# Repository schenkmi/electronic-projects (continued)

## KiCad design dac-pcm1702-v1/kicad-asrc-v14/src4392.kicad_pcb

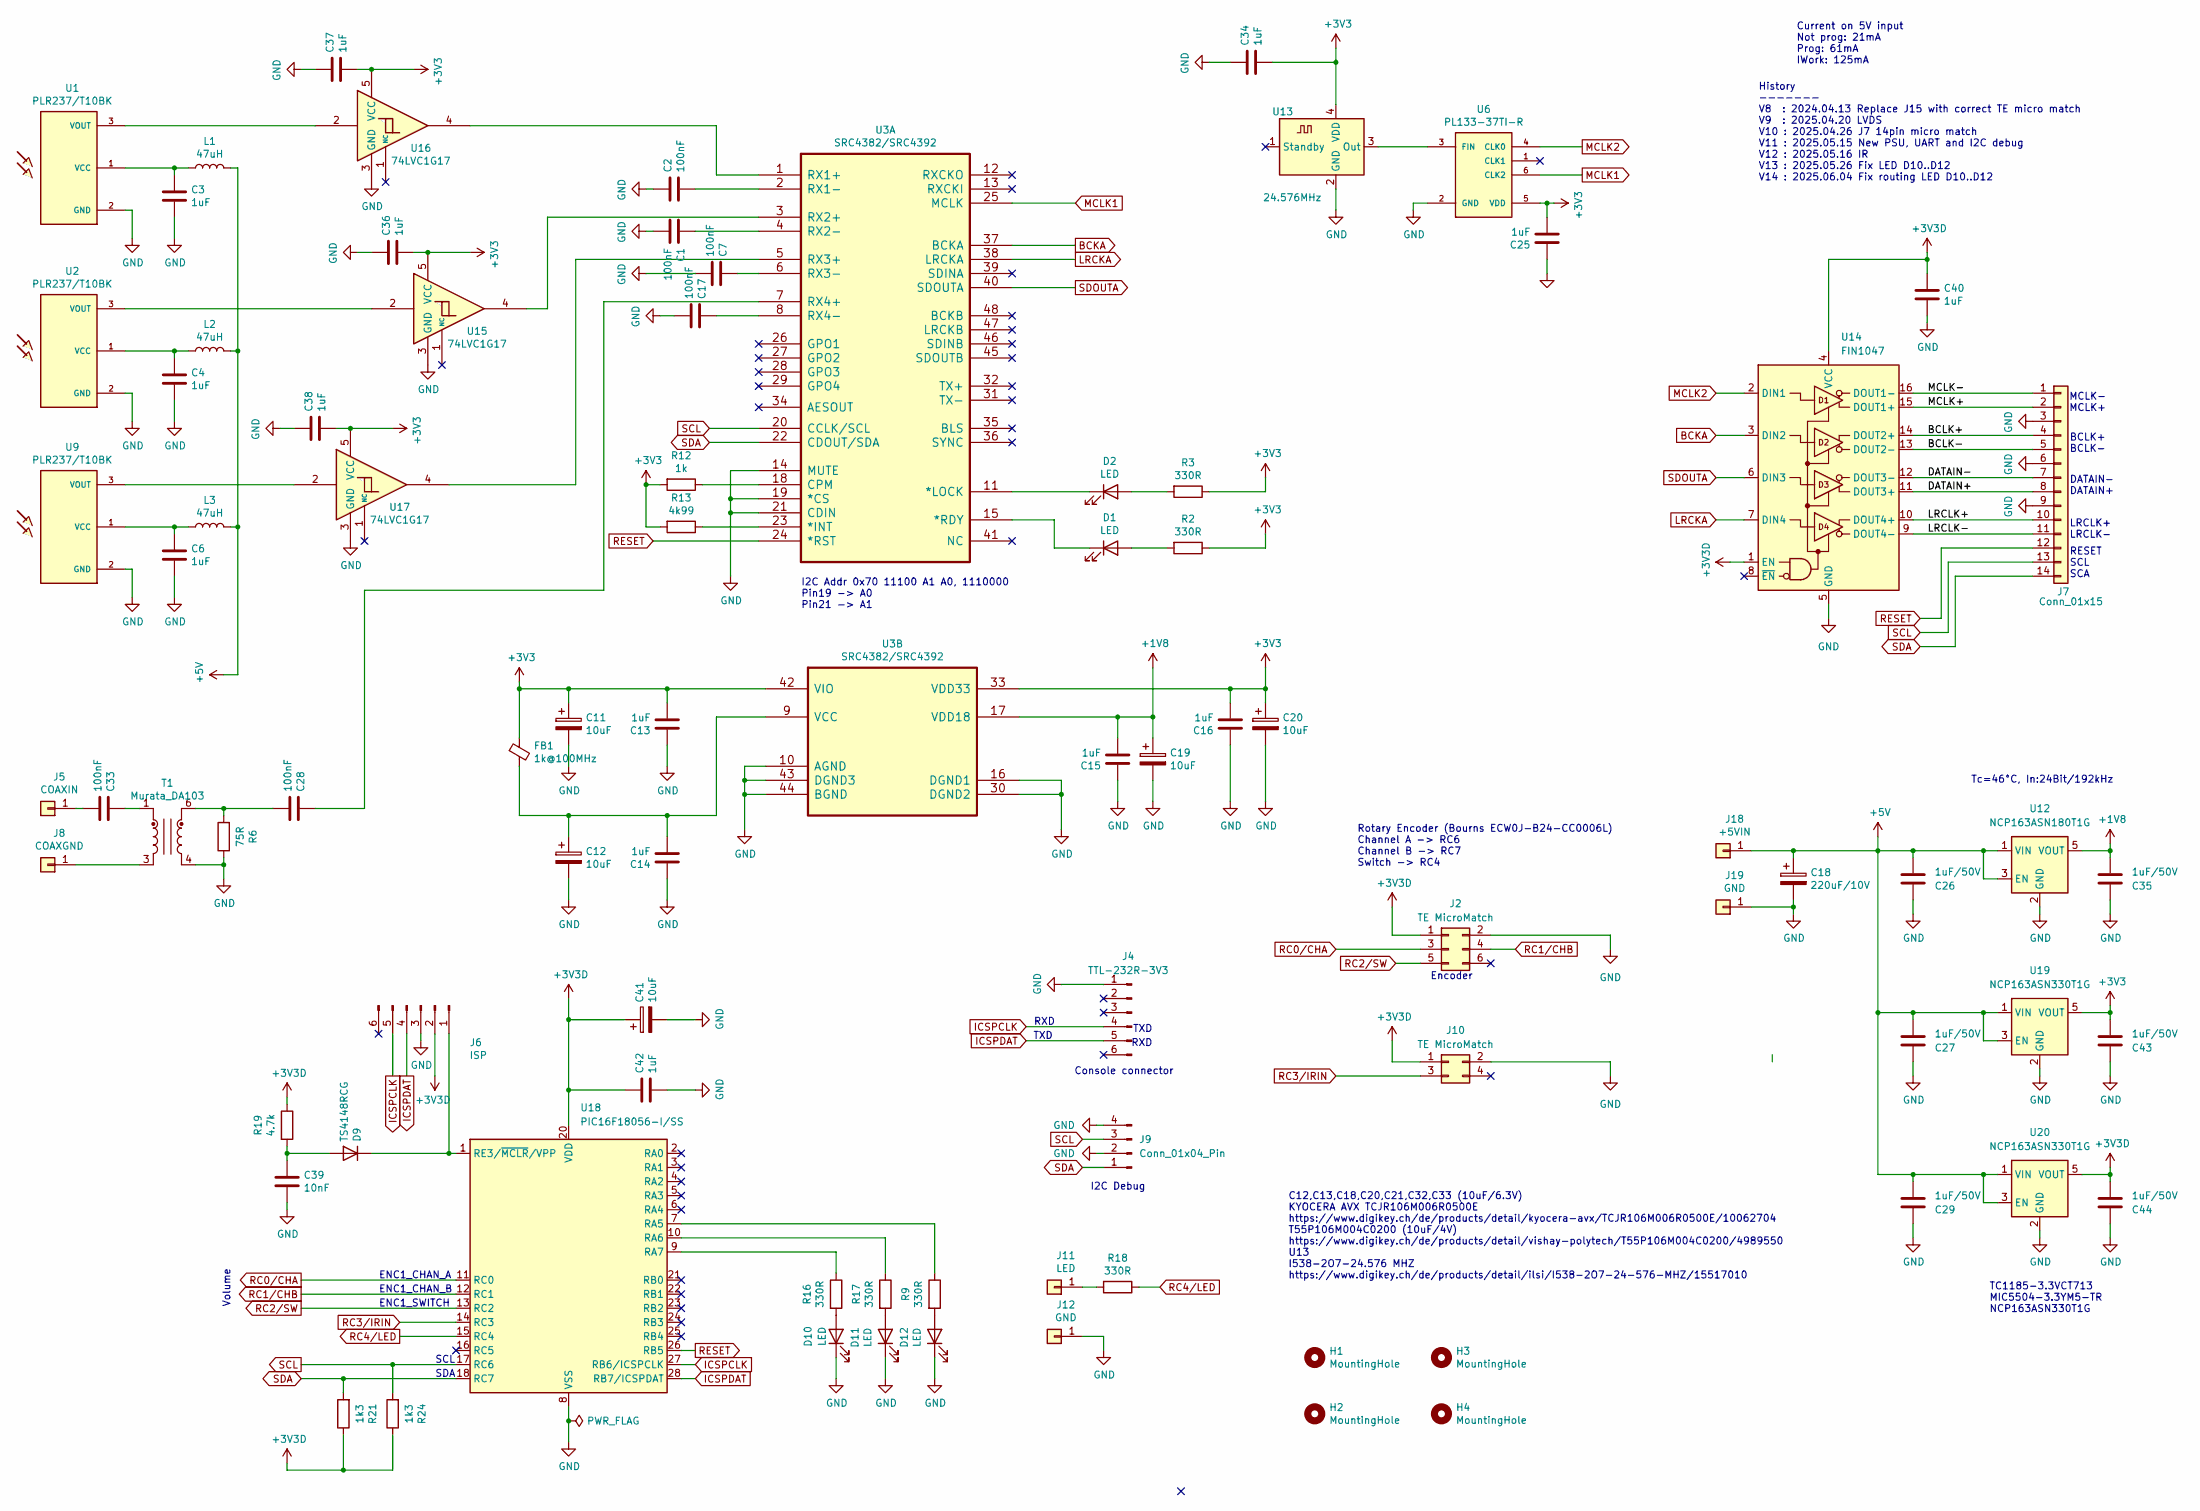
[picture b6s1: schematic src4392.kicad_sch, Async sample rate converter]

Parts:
C1, C2, C7, C17: 100nF; C_0402_1005Metric_Pad0.74x0.62mm_HandSolder
C3, C4, C6, C13, C14, C15, C16, C25, C34, C36, C37, C38, C40, C42: 1uF; C_0603_1608Metric_Pad1.08x0.95mm_HandSolder
C11, C12, C19, C20, C41: 10uF; CP_EIA-2012-12_Kemet-R_HandSolder
C18: 220uF/10V; CP_Radial_D6.3mm_P2.50mm
C26, C27, C29, C35, C43, C44: 1uF/50V; C_0805_2012Metric_Pad1.18x1.45mm_HandSolder
C28, C33: 100nF; C_0603_1608Metric_Pad1.08x0.95mm_HandSolder
C39: 10nF; C_0603_1608Metric_Pad1.08x0.95mm_HandSolder
D1, D2, D10, D11, D12: LED; LED_0603_1608Metric_Pad1.05x0.95mm_HandSolder
D9: TS4148RCG; D_0603_1608Metric_Pad1.05x0.95mm_HandSolder
FB1: 1k@100MHz; C_0603_1608Metric_Pad1.08x0.95mm_HandSolder
H1, H2, H3, H4: MountingHole; MountingHole_3.2mm_M3_Pad_Via
J2: TE MicroMatch; TE_Micro-MaTch_215079-6_2x03_P1.27mm_Vertical
J4: TTL-232R-3V3; PinHeader_1x06_P2.54mm_Vertical
J5: COAXIN; Pin_D1.0mm_L10.0mm
J6: ISP; PinHeader_1x06_P2.54mm_Vertical
J7: Conn_01x15; TE_Micro-MaTch_1-215079-4_2x07_P1.27mm_Vertical
J8: COAXGND; Pin_D1.0mm_L10.0mm
J9: Conn_01x04_Pin; PinHeader_1x04_P2.54mm_Vertical
J10: TE MicroMatch; TE_Micro-MaTch_215079-4_2x02_P1.27mm_Vertical
J11: LED; Pin_D1.0mm_L10.0mm
J12, J19: GND; Pin_D1.0mm_L10.0mm
J18: +5VIN; Pin_D1.0mm_L10.0mm
L1, L2, L3: 47uH; L_0805_2012Metric_Pad1.05x1.20mm_HandSolder
R2, R3, R9, R16, R17, R18: 330R; R_0603_1608Metric_Pad0.98x0.95mm_HandSolder
R6: 75R; R_0603_1608Metric_Pad0.98x0.95mm_HandSolder
R12: 1k; R_0402_1005Metric_Pad0.72x0.64mm_HandSolder
R13: 4k99; R_0402_1005Metric_Pad0.72x0.64mm_HandSolder
R19: 4.7k; R_0603_1608Metric_Pad0.98x0.95mm_HandSolder
R21, R24: 1k3; R_0603_1608Metric_Pad0.98x0.95mm_HandSolder
T1: Murata_DA103; DA100J
U1, U2, U9: PLR237/T10BK; PLR135-T10_PLT133-T10W
U3: SRC4382/SRC4392; TQFP-48_7x7mm_P0.5mm
U6: PL133-37TI-R; SOT-23-6
U12: NCP163ASN180T1G; SOT-23-5
U13: 24.576MHz; Oscillator_SMD_EuroQuartz_XO32-4Pin_3.2x2.5mm_RotB_HandSold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
U14: FIN1047; TSSOP-16_4.4x5mm_P0.65mm; Part Number FIN1047MTCX
U15, U16, U17: 74LVC1G17; SOT-23-5
U18: PIC16F18056-I/SS; SSOP-28_5.3x10.2mm_P0.65mm
U19, U20: NCP163ASN330T1G; SOT-23-5

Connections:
+1V8: C15.2, C19.1, C35.2, U3.17 (VDD18), U12.5 (VOUT)
+3V3: C11.1, C13.2, C16.2, C20.1, C25.2, C34.1, C36.1, C37.1, C38.1, C43.2, FB1.1, R2.1, R3.1, R12.2, R13.2, U3.33 (VDD33), U3.42 (VIO), U6.5 (VDD), U13.4 (VDD), U15.5 (VCC), U16.5 (VCC), U17.5 (VCC), U19.5 (VOUT)
+3V3D: C40.1, C41.1, C42.1, C44.2, J2.1, J6.2, J10.1, R19.1, R21.1, R24.1, U14.1 (EN), U14.4 (VCC), U18.20 (VDD), U20.5 (VOUT)
+5V: C18.1, C26.2, C27.2, C29.2, J18.1 (Pin_1_1), L1.2, L2.2, L3.2, U12.1 (VIN), U12.3 (EN), U19.1 (VIN), U19.3 (EN), U20.1 (VIN), U20.3 (EN)
/BCLK+: J7.4, U14.14 (DOUT2+)
/BCLK-: J7.5, U14.13 (DOUT2-)
/DATAIN+: J7.8, U14.11 (DOUT3+)
/DATAIN-: J7.7, U14.12 (DOUT3-)
/LRCLK+: J7.10, U14.10 (DOUT4+)
/LRCLK-: J7.11, U14.9 (DOUT4-)
/MCLK+: J7.2, U14.15 (DOUT1+)
/MCLK-: J7.1, U14.16 (DOUT1-)
BCKA: U3.37 (BCKA), U14.3 (DIN2)
GND: C1.1, C2.2, C3.1, C4.1, C6.1, C7.1, C11.2, C12.2, C13.1, C14.1, C15.1, C16.1, C17.1, C18.2, C19.2, C20.2, C25.1, C26.1, C27.1, C29.1, C34.2, C35.1, C36.2, C37.2, C38.2, C39.2, C40.2, C41.2, C42.2, C43.1, C44.1, D10.1 (K), D11.1 (K), D12.1 (K), J2.2, J4.1, J6.3, J7.3, J7.6, J7.9, J9.2, J9.4, J10.2, J12.1 (Pin_1_1), J19.1 (Pin_1_1), R6.1, T1.4, U1.2 (GND), U2.2 (GND), U3.10 (AGND), U3.14 (MUTE), U3.16 (DGND1), U3.19 (*CS), U3.21 (CDIN), U3.30 (DGND2), U3.43 (DGND3), U3.44 (BGND), U6.2 (GND), U9.2 (GND), U12.2 (GND), U13.2 (GND), U14.5 (GND), U15.3 (GND), U16.3 (GND), U17.3 (GND), U18.8 (VSS), U18.19 (VSS), U19.2 (GND), U20.2 (GND)
ICSPCLK: J4.4, J6.5, U18.27 (RB6/ICSPCLK)
ICSPDAT: J4.5, J6.4, U18.28 (RB7/ICSPDAT)
LRCKA: U3.38 (LRCKA), U14.7 (DIN4)
MCLK1: U3.25 (MCLK), U6.6 (CLK2)
MCLK2: U6.4 (CLK0), U14.2 (DIN1)
unnamed: C28.1, R6.2, T1.6
unnamed: C33.2, T1.1
unnamed: D1.2 (A), R2.2
unnamed: D1.1 (K), U3.15 (*RDY)
unnamed: D2.2 (A), R3.2
unnamed: D2.1 (K), U3.11 (*LOCK)
unnamed: C39.1, D9.2 (A), R19.2
unnamed: D9.1 (K), J6.1, U18.1 (RE3/~MCLR/VPP)
unnamed: D10.2 (A), R16.2
unnamed: D11.2 (A), R17.2
unnamed: D12.2 (A), R9.2
unnamed: C33.1, J5.1 (Pin_1_1)
unnamed: J8.1 (Pin_1_1), T1.3
unnamed: J11.1 (Pin_1_1), R18.2
unnamed: C3.2, L1.1, U1.1 (VCC)
unnamed: U1.3 (VOUT), U16.2
unnamed: C4.2, L2.1, U2.1 (VCC)
unnamed: U2.3 (VOUT), U15.2
unnamed: R13.1, U3.23 (*INT)
unnamed: R12.1, U3.18 (CPM)
unnamed: U3.1 (RX1+), U16.4
unnamed: C2.1, U3.2 (RX1-)
unnamed: U3.3 (RX2+), U15.4
unnamed: C1.2, U3.4 (RX2-)
unnamed: U3.5 (RX3+), U17.4
unnamed: C7.2, U3.6 (RX3-)
unnamed: C28.2, U3.7 (RX4+)
unnamed: C17.2, U3.8 (RX4-)
unnamed: C12.1, C14.2, FB1.2, U3.9 (VCC)
unnamed: C6.2, L3.1, U9.1 (VCC)
unnamed: U9.3 (VOUT), U17.2
unnamed: U6.3 (FIN), U13.3 (Out)
unnamed: R9.1, U18.7 (RA5)
unnamed: R17.1, U18.10 (RA6)
unnamed: R16.1, U18.9 (RA7)
RC0/CHA: J2.3, U18.11 (RC0)
RC1/CHB: J2.4, U18.12 (RC1)
RC2/SW: J2.5, U18.13 (RC2)
RC3/IRIN: J10.3, U18.14 (RC3)
RC4/LED: R18.1, U18.15 (RC4)
RESET: J7.12, U3.24 (*RST), U18.26 (RB5)
SCL: J7.13, J9.3, R24.2, U3.20 (CCLK/SCL), U18.17 (RC6)
SDA: J7.14, J9.1, R21.2, U3.22 (CDOUT/SDA), U18.18 (RC7)
SDOUTA: U3.40 (SDOUTA), U14.6 (DIN3)

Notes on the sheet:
ENC1_CHAN_B
I2C Addr 0x70 11100 A1 A0, 1110000 Pin19 -> A0 Pin21 -> A1
History ------- V8 : 2024.04.13 Replace J15 with correct TE micro match V9 : 2025.04.20 LVDS V10 : 2025.04.26 J7 14pin micro match V11 : 2025.05.15 New PSU, UART and I2C debug V12 : 2025.05.16 IR V13 : 2025.05.26 Fix LED D10..D12 V14 : 2025.06.04 Fix routing LED D10..D12
ENC1_CHAN_A
Console connector
SDA
DATAIN- DATAIN+
LRCLK+ LRCLK-
MCLK- MCLK+
TC1185-3.3VCT713 MIC5504-3.3YM5-TR NCP163ASN330T1G
ENC1_SWITCH
RXD
Rotary Encoder (Bourns ECW0J-B24-CC0006L) Channel A -> RC6 Channel B -> RC7 Switch -> RC4
Volume
BCLK+ BCLK-
Tc=46°C, In:24Bit/192kHz
Encoder
Current on 5V input Not prog: 21mA Prog: 61mA IWork: 125mA
C12,C13,C18,C20,C21,C32,C33 (10uF/6.3V) KYOCERA AVX TCJR106M006R0500E https://www.digikey.ch/de/products/detail/kyocera-avx/TCJR106M006R0500E/10062704 T55P106M004C0200 (10uF/4V) https://www.digikey.ch/de/products/detail/vishay-polytech/T55P106M004C0200/4989550 U13 I538-2O7-24.576 MHZ https://www.di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
I2C Debug
TXD
SCL
RESET SCL SCA

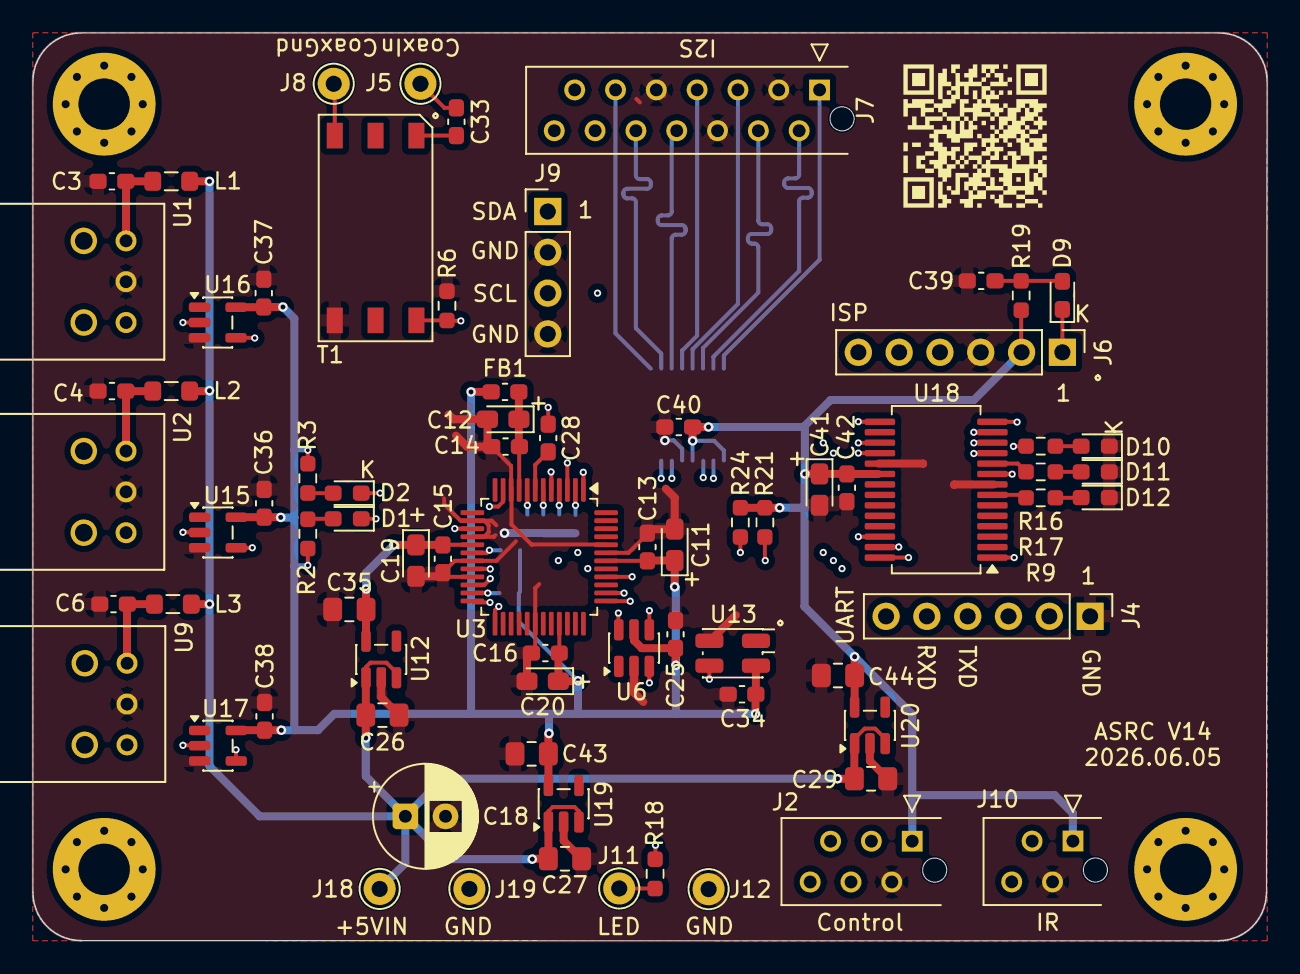
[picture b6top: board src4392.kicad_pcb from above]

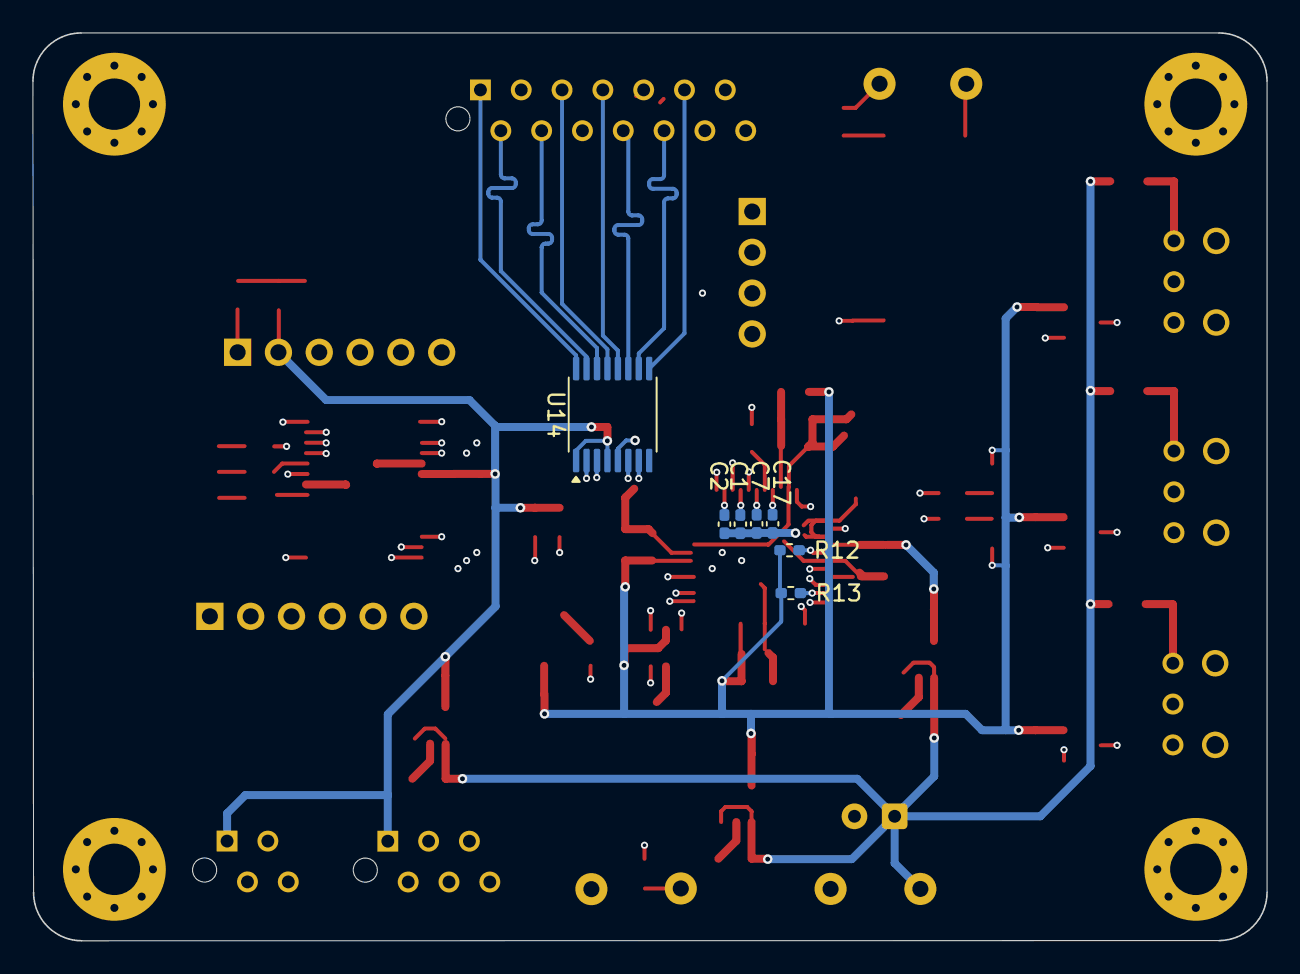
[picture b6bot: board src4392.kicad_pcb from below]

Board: 4 copper layers, 76.8 x 56.5 mm, 86 parts (7 on the bottom side), 63 nets.

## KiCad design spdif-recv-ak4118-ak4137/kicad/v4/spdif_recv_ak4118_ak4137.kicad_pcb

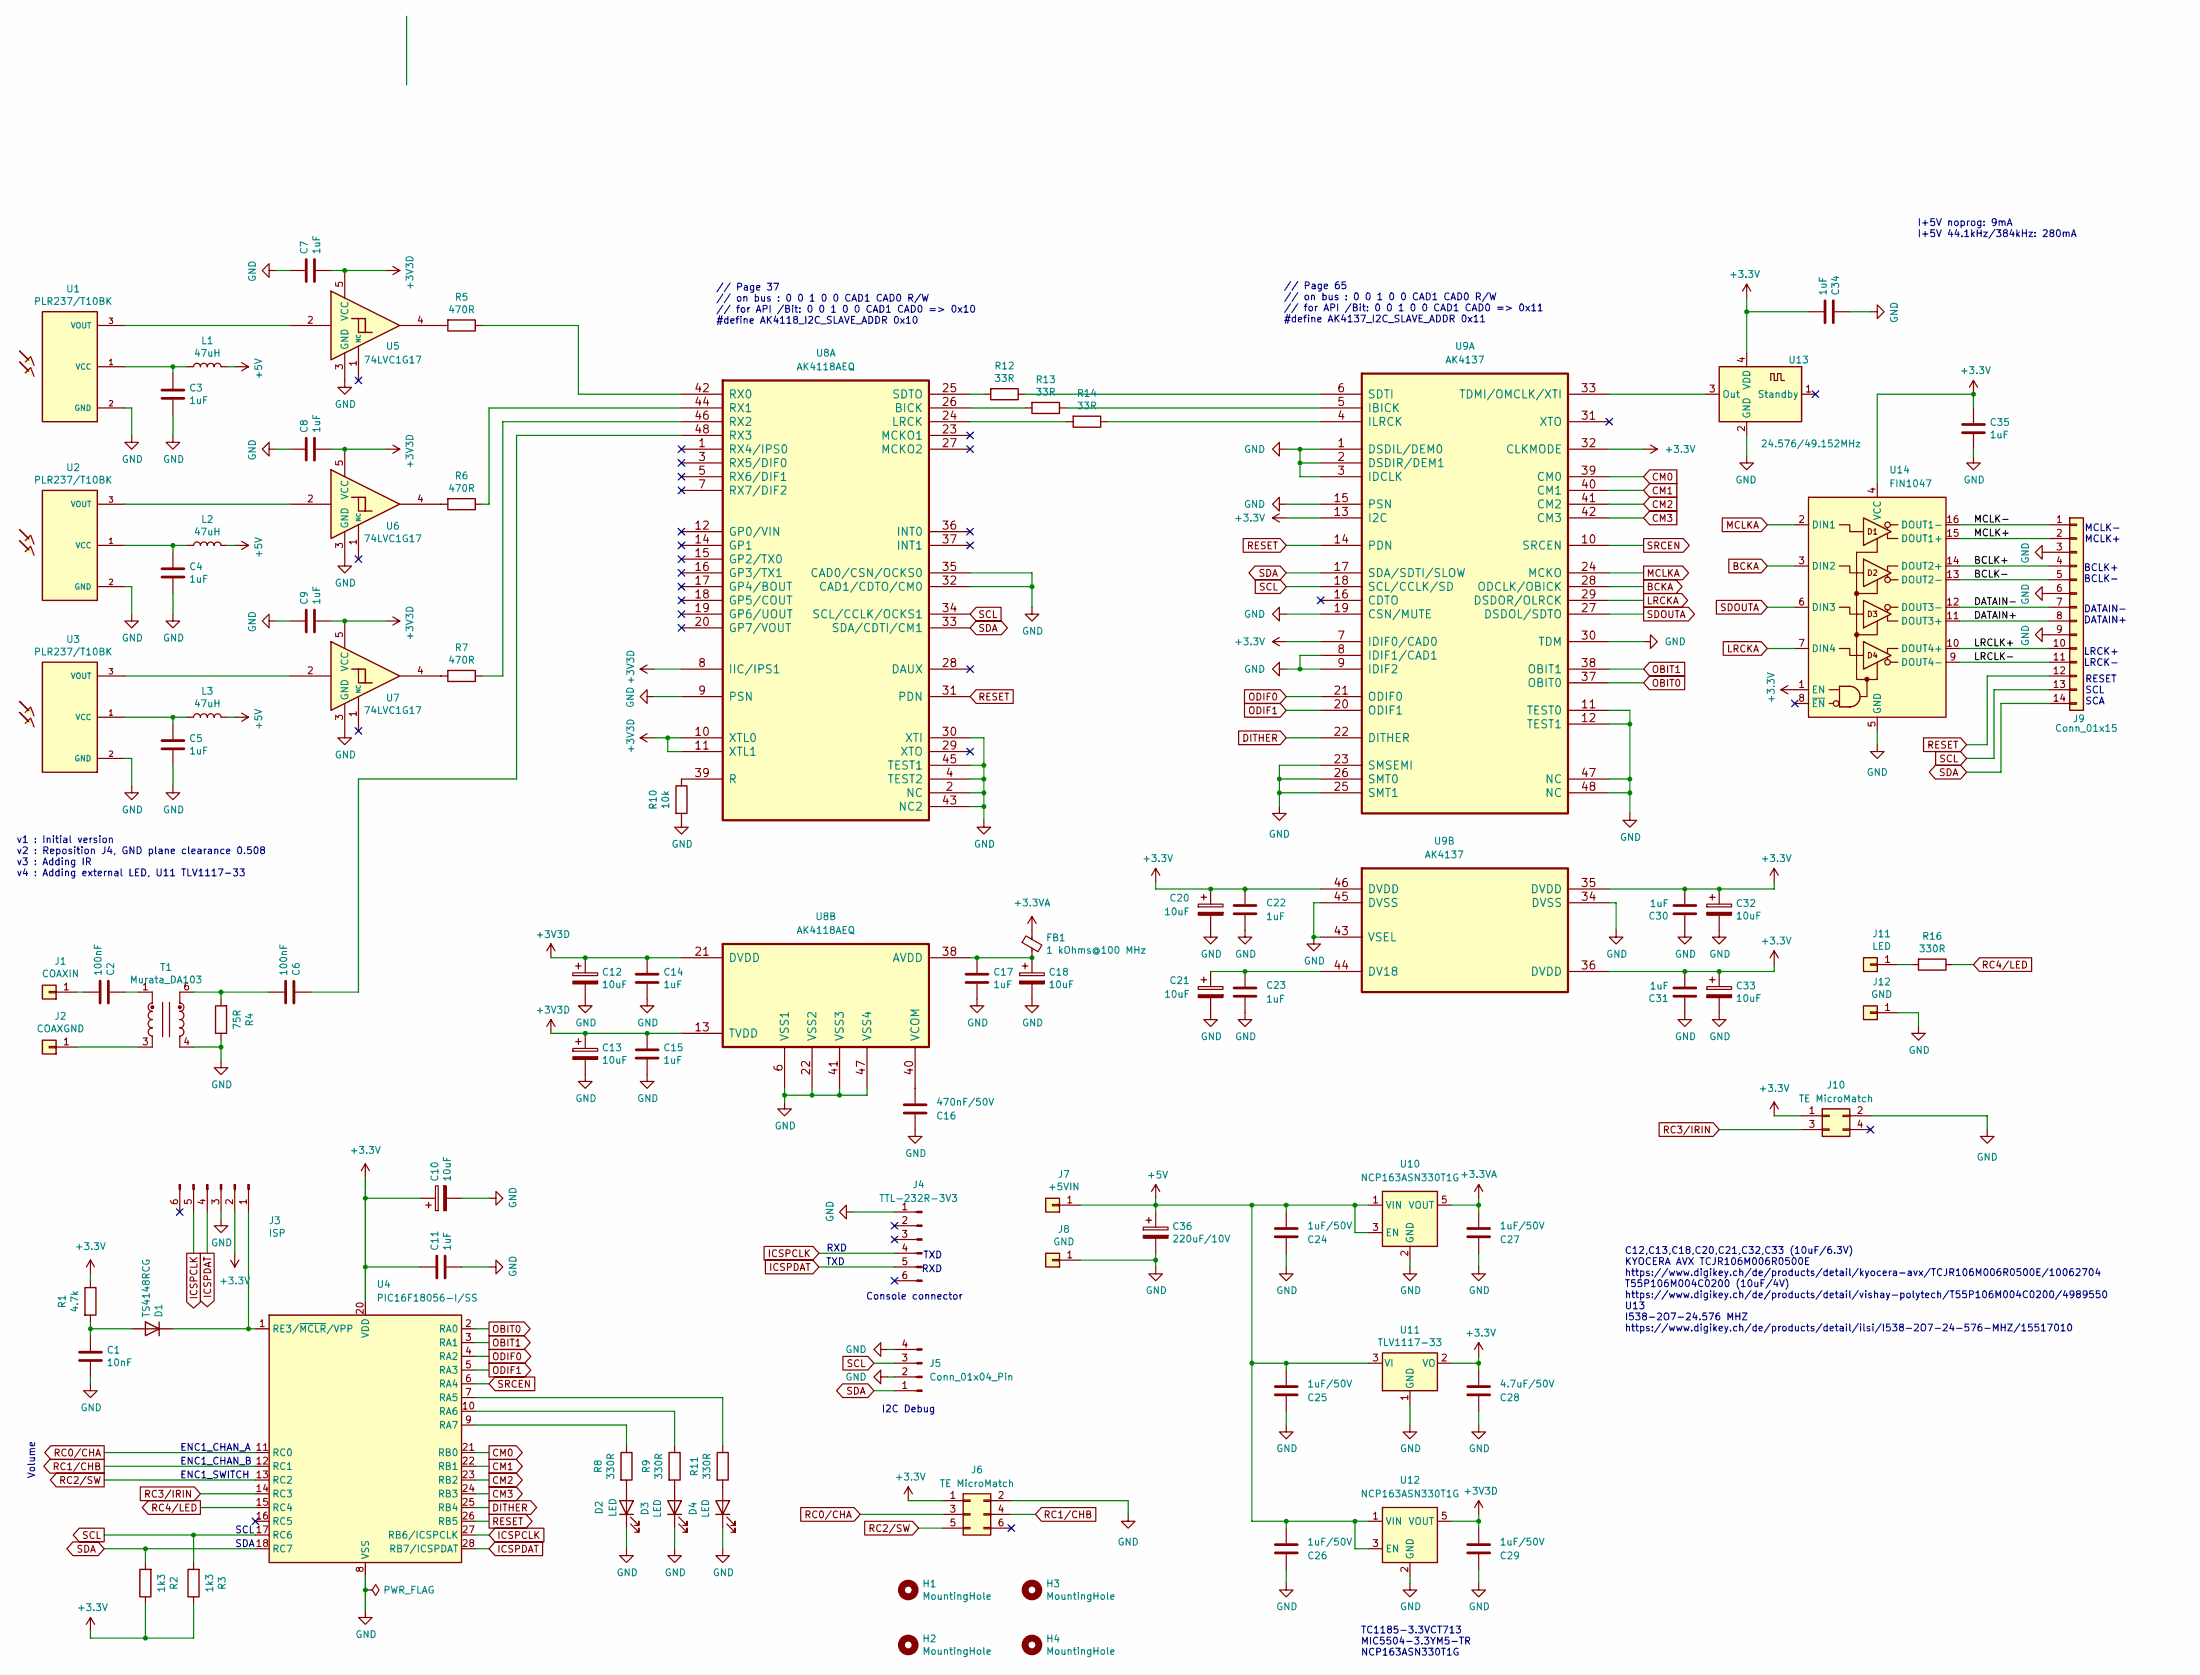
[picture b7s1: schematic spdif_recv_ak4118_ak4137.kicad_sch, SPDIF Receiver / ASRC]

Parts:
C1: 10nF; C_0603_1608Metric_Pad1.08x0.95mm_HandSolder
C2, C6: 100nF; C_0603_1608Metric_Pad1.08x0.95mm_HandSolder
C3, C4, C5, C7, C8, C9, C11, C14, C15, C17, C22, C23, C30, C31, C34, C35: 1uF; C_0603_1608Metric_Pad1.08x0.95mm_HandSolder
C10, C12, C13, C18, C20, C21, C32, C33: 10uF; CP_EIA-2012-12_Kemet-R_HandSolder
C16: 470nF/50V; C_0805_2012Metric_Pad1.18x1.45mm_HandSolder
C24, C25, C26, C27, C29: 1uF/50V; C_0805_2012Metric_Pad1.18x1.45mm_HandSolder
C28: 4.7uF/50V; C_1206_3216Metric_Pad1.33x1.80mm_HandSolder
C36: 220uF/10V; CP_Radial_D6.3mm_P2.50mm
D1: TS4148RCG; D_0603_1608Metric_Pad1.05x0.95mm_HandSolder
D2, D3, D4: LED; LED_0603_1608Metric_Pad1.05x0.95mm_HandSolder
FB1: 1 kOhms@100 MHz; C_0603_1608Metric_Pad1.08x0.95mm_HandSolder
H1, H2, H3, H4: MountingHole; MountingHole_3.2mm_M3_Pad_Via
J1: COAXIN; Pin_D1.0mm_L10.0mm
J2: COAXGND; Pin_D1.0mm_L10.0mm
J3: ISP; PinHeader_1x06_P2.54mm_Vertical
J4: TTL-232R-3V3; PinHeader_1x06_P2.54mm_Vertical
J5: Conn_01x04_Pin; PinHeader_1x04_P2.54mm_Vertical
J6: TE MicroMatch; TE_Micro-MaTch_215079-6_2x03_P1.27mm_Vertical
J7: +5VIN; Pin_D1.0mm_L10.0mm
J8, J12: GND; Pin_D1.0mm_L10.0mm
J9: Conn_01x15; TE_Micro-MaTch_1-215079-4_2x07_P1.27mm_Vertical
J10: TE MicroMatch; TE_Micro-MaTch_215079-4_2x02_P1.27mm_Vertical
J11: LED; Pin_D1.0mm_L10.0mm
L1, L2, L3: 47uH; L_0805_2012Metric_Pad1.05x1.20mm_HandSolder
R1: 4.7k; R_0603_1608Metric_Pad0.98x0.95mm_HandSolder
R2, R3: 1k3; R_0603_1608Metric_Pad0.98x0.95mm_HandSolder
R4: 75R; R_0603_1608Metric_Pad0.98x0.95mm_HandSolder
R5, R6, R7: 470R; R_0603_1608Metric_Pad0.98x0.95mm_HandSolder
R8, R9, R11, R16: 330R; R_0603_1608Metric_Pad0.98x0.95mm_HandSolder
R10: 10k; R_0603_1608Metric_Pad0.98x0.95mm_HandSolder
R12, R13, R14: 33R; R_0402_1005Metric_Pad0.72x0.64mm_HandSolder
T1: Murata_DA103; DA100J
U1, U2, U3: PLR237/T10BK; PLR135-T10_PLT133-T10W
U4: PIC16F18056-I/SS; SSOP-28_5.3x10.2mm_P0.65mm
U5, U6, U7: 74LVC1G17; SOT-23-5
U8: AK4118AEQ; LQFP-48_7x7mm_P0.5mm
U9: AK4137; LQFP-48_7x7mm_P0.5mm
U10, U12: NCP163ASN330T1G; SOT-23-5
U11: TLV1117-33; SOT-223-3_TabPin2
U13: 24.576/49.152MHz; Oscillator_SMD_EuroQuartz_XO32-4Pin_3.2x2.5mm_RotB_HandSold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
U14: FIN1047; TSSOP-16_4.4x5mm_P0.65mm; Part Number FIN1047MTCX

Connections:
+3.3V: C10.1, C11.1, C20.1, C22.2, C28.2, C30.2, C31.2, C32.1, C33.1, C34.1, C35.1, J3.2, J6.1, J10.1, R1.1, R2.1, R3.1, U4.20 (VDD), U9.7 (IDIF0/CAD0), U9.13 (I2C), U9.32 (CLKMODE), U9.35 (DVDD), U9.36 (DVDD), U9.46 (DVDD), U11.2 (VO), U13.4 (VDD), U14.1 (EN), U14.4 (VCC)
+3.3VA: C27.2, FB1.1, U10.5 (VOUT)
+3V3D: C7.1, C8.1, C9.1, C12.1, C13.1, C14.1, C15.1, C29.2, U5.5 (VCC), U6.5 (VCC), U7.5 (VCC), U8.8 (IIC/IPS1), U8.10 (XTL0), U8.11 (XTL1), U8.13 (TVDD), U8.21 (DVDD), U12.5 (VOUT)
+5V: C24.2, C25.2, C26.2, C36.1, J7.1 (Pin_1_1), L1.2, L2.2, L3.2, U10.1 (VIN), U10.3 (EN), U11.3 (VI), U12.1 (VIN), U12.3 (EN)
/BCLK+: J9.4, U14.14 (DOUT2+)
/BCLK-: J9.5, U14.13 (DOUT2-)
/DATAIN+: J9.8, U14.11 (DOUT3+)
/DATAIN-: J9.7, U14.12 (DOUT3-)
/LRCLK+: J9.10, U14.10 (DOUT4+)
/LRCLK-: J9.11, U14.9 (DOUT4-)
/MCLK+: J9.2, U14.15 (DOUT1+)
/MCLK-: J9.1, U14.16 (DOUT1-)
BCKA: U9.28 (ODCLK/OBICK), U14.3 (DIN2)
CM0: U4.21 (RB0), U9.39 (CM0)
CM1: U4.22 (RB1), U9.40 (CM1)
CM2: U4.23 (RB2), U9.41 (CM2)
CM3: U4.24 (RB3), U9.42 (CM3)
DITHER: U4.25 (RB4), U9.22 (DITHER)
GND: C1.2, C3.1, C4.1, C5.1, C7.2, C8.2, C9.2, C10.2, C11.2, C12.2, C13.2, C14.2, C15.2, C16.1, C17.2, C18.2, C20.2, C21.2, C22.1, C23.1, C24.1, C25.1, C26.1, C27.1, C28.1, C29.1, C30.1, C31.1, C32.2, C33.2, C34.2, C35.2, C36.2, D2.1 (K), D3.1 (K), D4.1 (K), J3.3, J4.1, J5.2, J5.4, J6.2, J8.1 (Pin_1_1), J9.3, J9.6, J9.9, J10.2, J12.1 (Pin_1_1), R4.1, R10.2, T1.4, U1.2 (GND), U2.2 (GND), U3.2 (GND), U4.8 (VSS), U4.19 (VSS), U5.3 (GND), U6.3 (GND), U7.3 (GND), U8.2 (NC), U8.4 (TEST2), U8.6 (VSS1), U8.9 (PSN), U8.22 (VSS2), U8.30 (XTI), U8.32 (CAD1/CDTO/CM0), U8.35 (CAD0/CSN/OCKS0), U8.41 (VSS3), U8.43 (NC2), U8.45 (TEST1), U8.47 (VSS4), U9.1 (DSDIL/DEM0), U9.2 (DSDIR/DEM1), U9.3 (IDCLK), U9.8 (IDIF1/CAD1), U9.9 (IDIF2), U9.11 (TEST0), U9.12 (TEST1), U9.15 (PSN), U9.19 (CSN/MUTE), U9.23 (SMSEMI), U9.25 (SMT1), U9.26 (SMT0), U9.30 (TDM), U9.34 (DVSS), U9.43 (VSEL), U9.45 (DVSS), U9.47 (NC), U9.48 (NC), U10.2 (GND), U11.1 (GND), U12.2 (GND), U13.2 (GND), U14.5 (GND)
ICSPCLK: J3.5, J4.4, U4.27 (RB6/ICSPCLK)
ICSPDAT: J3.4, J4.5, U4.28 (RB7/ICSPDAT)
LRCKA: U9.29 (DSDOR/OLRCK), U14.7 (DIN4)
MCLKA: U9.24 (MCKO), U14.2 (DIN1)
unnamed: C2.2, T1.1
unnamed: C6.1, R4.2, T1.6
unnamed: C1.1, D1.2 (A), R1.2
unnamed: D1.1 (K), J3.1, U4.1 (RE3/~MCLR/VPP)
unnamed: D2.2 (A), R8.2
unnamed: D3.2 (A), R9.2
unnamed: D4.2 (A), R11.2
unnamed: C2.1, J1.1 (Pin_1_1)
unnamed: J2.1 (Pin_1_1), T1.3
unnamed: J11.1 (Pin_1_1), R16.2
unnamed: R5.2, U5.4
unnamed: R6.2, U6.4
unnamed: R7.2, U7.4
unnamed: C3.2, L1.1, U1.1 (VCC)
unnamed: U1.3 (VOUT), U5.2
unnamed: C4.2, L2.1, U2.1 (VCC)
unnamed: U2.3 (VOUT), U6.2
unnamed: C5.2, L3.1, U3.1 (VCC)
unnamed: U3.3 (VOUT), U7.2
unnamed: R11.1, U4.7 (RA5)
unnamed: R9.1, U4.10 (RA6)
unnamed: R8.1, U4.9 (RA7)
unnamed: R13.2, U8.26 (BICK)
unnamed: R14.2, U8.24 (LRCK)
unnamed: R10.1, U8.39 (R)
unnamed: R5.1, U8.42 (RX0)
unnamed: R6.1, U8.44 (RX1)
unnamed: R7.1, U8.46 (RX2)
unnamed: C6.2, U8.48 (RX3)
unnamed: R12.2, U8.25 (SDTO)
unnamed: C17.1, C18.1, FB1.2, U8.38 (AVDD)
unnamed: C16.2, U8.40 (VCOM)
unnamed: R13.1, U9.5 (IBICK)
unnamed: R14.1, U9.4 (ILRCK)
unnamed: R12.1, U9.6 (SDTI)
unnamed: C21.1, C23.2, U9.44 (DV18)
unnamed: U9.33 (TDMI/OMCLK/XTI), U13.3 (Out)
OBIT0: U4.2 (RA0), U9.37 (OBIT0)
OBIT1: U4.3 (RA1), U9.38 (OBIT1)
ODIF0: U4.4 (RA2), U9.21 (ODIF0)
ODIF1: U4.5 (RA3), U9.20 (ODIF1)
RC0/CHA: J6.3, U4.11 (RC0)
RC1/CHB: J6.4, U4.12 (RC1)
RC2/SW: J6.5, U4.13 (RC2)
RC3/IRIN: J10.3, U4.14 (RC3)
RC4/LED: R16.1, U4.15 (RC4)
RESET: J9.12, U4.26 (RB5), U8.31 (PDN), U9.14 (PDN)
SCL: J5.3, J9.13, R3.2, U4.17 (RC6), U8.34 (SCL/CCLK/OCKS1), U9.18 (SCL/CCLK/SD)
SDA: J5.1, J9.14, R2.2, U4.18 (RC7), U8.33 (SDA/CDTI/CM1), U9.17 (SDA/SDTI/SLOW)
SDOUTA: U9.27 (DSDOL/SDTO), U14.6 (DIN3)
SRCEN: U4.6 (RA4), U9.10 (SRCEN)

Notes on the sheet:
I2C Debug
// Page 65 // on bus : 0 0 1 0 0 CAD1 CAD0 R/W // for API /Bit: 0 0 1 0 0 CAD1 CAD0 => 0x11 #define AK4137_I2C_SLAVE_ADDR 0x11
ENC1_CHAN_A
SDA
TC1185-3.3VCT713 MIC5504-3.3YM5-TR NCP163ASN330T1G
MCLK- MCLK+
RXD
DATAIN- DATAIN+
BCLK+ BCLK-
// Page 37 // on bus : 0 0 1 0 0 CAD1 CAD0 R/W // for API /Bit: 0 0 1 0 0 CAD1 CAD0 => 0x10 #define AK4118_I2C_SLAVE_ADDR 0x10
Volume
LRCK+ LRCK-
SCL
I+5V noprog: 9mA I+5V 44.1kHz/384kHz: 280mA
v1 : Initial version v2 : Reposition J4, GND plane clearance 0.508 v3 : Adding IR v4 : Adding external LED, U11 TLV1117-33
RESET SCL SCA
TXD
C12,C13,C18,C20,C21,C32,C33 (10uF/6.3V) KYOCERA AVX TCJR106M006R0500E https://www.digikey.ch/de/products/detail/kyocera-avx/TCJR106M006R0500E/10062704 T55P106M004C0200 (10uF/4V) https://www.digikey.ch/de/products/detail/vishay-polytech/T55P106M004C0200/4989550 U13 I538-2O7-24.576 MHZ https://www.di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
ENC1_SWITCH
Console connector
ENC1_CHAN_B

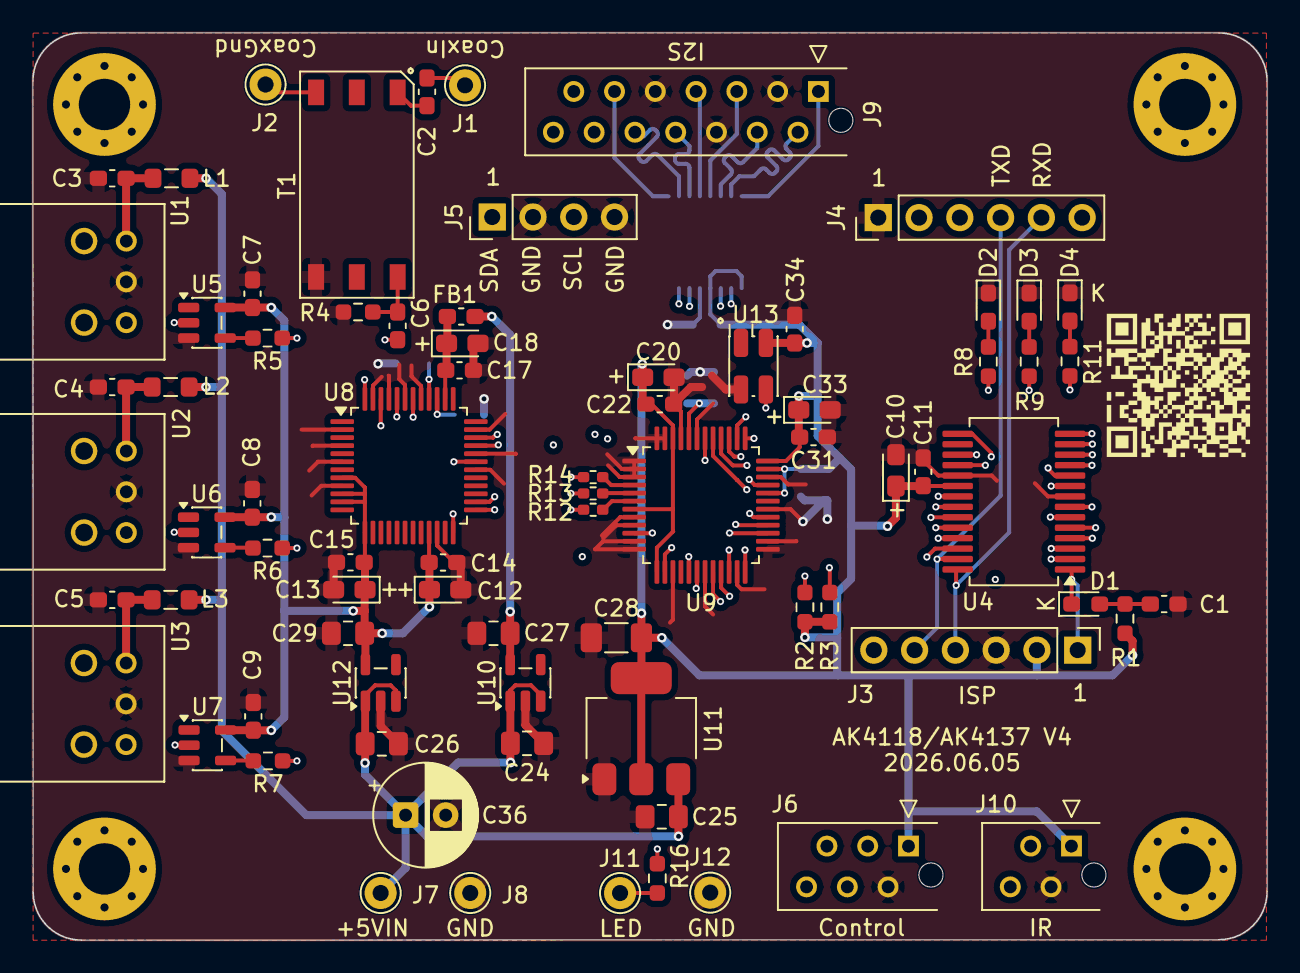
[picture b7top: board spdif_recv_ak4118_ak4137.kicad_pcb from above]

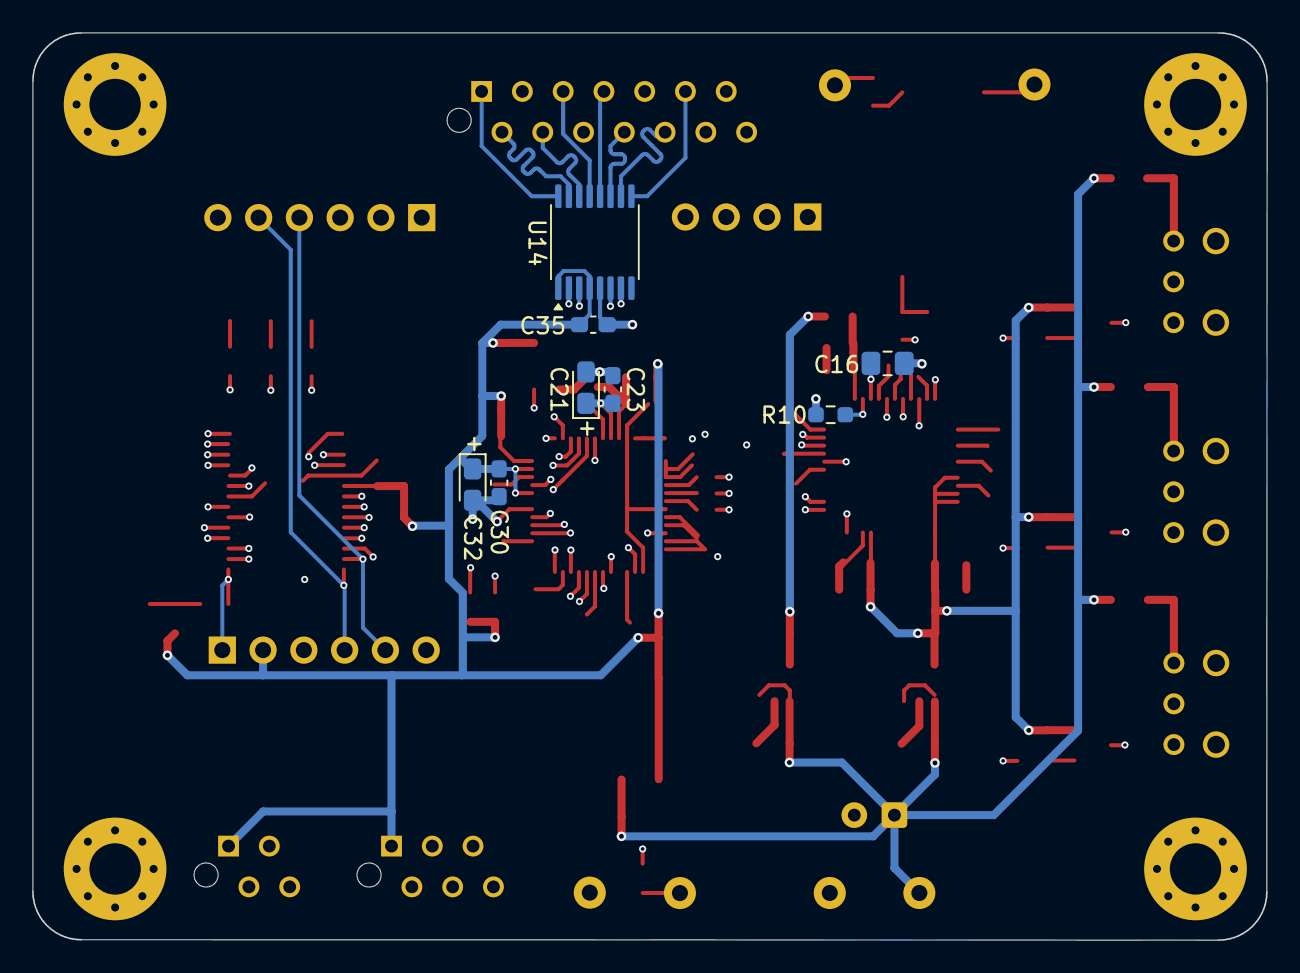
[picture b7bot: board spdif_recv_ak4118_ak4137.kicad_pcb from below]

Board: 4 copper layers, 76.9 x 56.5 mm, 89 parts (8 on the bottom side), 74 nets.

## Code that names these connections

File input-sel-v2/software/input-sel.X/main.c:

/**
  Generated Main Source File

  Company:
    Microchip Technology Inc.

  File Name:
    main.c

  Summary:
    This is the main file generated using PIC10 / PIC12 / PIC16 / PIC18 MCUs

  Description:
    This header file provides implementations for driver APIs for all modules selected in the GUI.
    Generation Information :
        Product Revision  :  PIC10 / PIC12 / PIC16 / PIC18 MCUs - 1.81.6
        Device            :  PIC16F18446
        Driver Version    :  2.00
*/

/*
    (c) 2018 Microchip Technology Inc. and its subsidiaries. 
    
    Subject to your compliance with these terms, you may use Microchip software and any 
    derivatives exclusively with Microchip products. It is your responsibility to comply with third party 
    license terms applicable to your use of third party software (including open source software) that 
    may accompany Microchip software.
    
    THIS SOFTWARE IS SUPPLIED BY MICROCHIP "AS IS". NO WARRANTIES, WHETHER 
    EXPRESS, IMPLIED OR STATUTORY, APPLY TO THIS SOFTWARE, INCLUDING ANY 
    IMPLIED WARRANTIES OF NON-INFRINGEMENT, MERCHANTABILITY, AND FITNESS 
    FOR A PARTICULAR PURPOSE.
    
    IN NO EVENT WILL MICROCHIP BE LIABLE FOR ANY INDIRECT, SPECIAL, PUNITIVE, 
    INCIDENTAL OR CONSEQUENTIAL LOSS, DAMAGE, COST OR EXPENSE OF ANY KIND 
    WHATSOEVER RELATED TO THE SOFTWARE, HOWEVER CAUSED, EVEN IF MICROCHIP 
    HAS BEEN ADVISED OF THE POSSIBILITY OR THE DAMAGES ARE FORESEEABLE. TO 
    THE FULLEST EXTENT ALLOWED BY LAW, MICROCHIP'S TOTAL LIABILITY ON ALL 
    CLAIMS IN ANY WAY RELATED TO THIS SOFTWARE WILL NOT EXCEED THE AMOUNT 
    OF FEES, IF ANY, THAT YOU HAVE PAID DIRECTLY TO MICROCHIP FOR THIS 
    SOFTWARE.
*/

#include "mcc_generated_files/mcc.h"

#define SELIN1 PORTCbits.RC0
#define SELIN2 PORTCbits.RC1
#define SELIN3 PORTCbits.RC2
#define SELIN4 PORTCbits.RC3
#define MUTEOUT PORTCbits.RC4

#define MUTE_OFF_BIT    0x10

#define LED PORTAbits.RA4

static void eeprom_example(void)
{
    volatile uint8_t value = 0x09;
    uint8_t address = 0xE5;
    eeprom_write(address, value);     // Writing value 0x9 to EEPROM address 0xE5        
    value = eeprom_read (address);    // Reading the value from address 0xE5
}

static int get_chan_sel(void)
{
    int ret = -1;
    /**
     * PORTB weak pull-up RB7..RB4
     * Input selector ties to GND so we invert the bits here
     */
    uint8_t input = (~(PORTB >> 4)) & 0x0f;
    
    switch (input) {
        case 0x01: /* INPUT 1, RB4 tie to GND */
            ret = 0;
            break;
        case 0x02: /* INPUT 2, RB5 tie to GND */
            ret = 1;
            break;
        case 0x04: /* INPUT 3, RB6 tie to GND */
            ret = 2;
            break;
        case 0x08: /* INPUT 4, RB7 tie to GND */
            ret = 3;
            break;
        default:
            break;
    }
    
    return ret;
}

void init(void)
{    
    PORTC = 0;
    LED = 1;
    
    /* one channel after the others */
    for (int cnt = 0; cnt < 4; cnt++) {
        uint8_t in = ((1 << cnt) & 0xff);
        PORTC |= in;
        __delay_ms(500);
        PORTC &= ~in;
    }
}

/*
                         Main application
 */
void main(void)
{
    int selected = -1;
    int last_selected = -1; 
    
    
    // initialize the device
    SYSTEM_Initialize();

    // When using interrupts, you need to set the Global and Peripheral Interrupt Enable bits
    // Use the following macros to:

    // Enable the Global Interrupts
    //INTERRUPT_GlobalInterruptEnable();

    // Enable the Peripheral Interrupts
    //INTERRUPT_PeripheralInterruptEnable();

    // Disable the Global Interrupts
    //INTERRUPT_GlobalInterruptDisable();

    // Disable the Peripheral Interrupts
    //INTERRUPT_PeripheralInterruptDisable();
    
    init();

    
    while (1) {
        __delay_ms(20);
        selected = get_chan_sel();
        if (selected == -1) {
            continue;
        }
        
        if (selected != last_selected) {
                        PORTC &= ~((1 << last_selected) & 0xff);
            PORTC |= (((1 << selected) & 0xff) | MUTE_OFF_BIT);
            last_selected = selected;
        }
        
        


    }
}
/**
 End of File
*/

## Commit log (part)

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2026-03-29 V1 completed
2026-04-08 Update after building
2026-04-15 Add description and update to KiCad 10
2026-04-16 Update and migrate to KiCad 10
2026-04-21 Redesign of AK4118AEQ KiCad schematic symbol
2026-04-21 Start with SPDIF receiver AK4118 AK4137
2026-04-21 Start with SPDIF receiver AK4118/4137
2026-04-21 Adding AK4118AEQ SPDIF Receiver
2026-04-24 Finalize layout
2026-04-24 Finalize v2
2026-04-24 Start with v7
2026-04-26 Update after measurement with real toroidal transformer
2026-05-03 Verilog simulation
2026-05-03 Rename
2026-05-05 migrate from CS8416 to AK4118
2026-05-06 Added UART support
2026-05-06 Adding some software resources related to AK4118
2026-05-07 LTSpice Simulation
2026-05-10 first working version AK4118/AK4137
2026-05-10 add compiled hex file
2026-05-10 V2 finalize
2026-05-10 Finalize v7
2026-05-10 Infos about oszillator
2026-05-11 Start with V11
2026-05-15 Ready to order
2026-05-16 Finalize V3 with IR
2026-05-16 Finalize V12
2026-05-18 Start with V3 Software
2026-05-18 Update header
2026-05-18 Start with V3
2026-05-26 start with new software for ASRC4392 V12
2026-05-26 reimplement ASRC4392
2026-05-26 fix I2C
2026-05-27 None TO-220 FET
2026-05-27 Start with v13
2026-05-28 Created gerber files for V13
2026-05-31 finalize i2s-nos-dac I2S to PCM1704/PCM1702 V7
2026-05-31 measurements
2026-05-31 power up only A and required blocks, rest leave in power down
2026-05-31 fix switch Channel/Volume
2026-06-03 Update DFP and MCC
2026-06-04 V14 with PCB trace fix toward LEDs
2026-06-04 disable printf
2026-06-04 Starting with V3
2026-06-04 Introducing callbacks
2026-06-05 Finalize V4
2026-06-05 Finalize V14
2026-06-05 Finalize V8
2026-06-10 Add LED_EXT GPIO
2026-06-10 Cleanup
2026-06-17 Start SPDIF ASRC 4392 V14
2026-06-17 Configure 4392 and EXT LED handling
